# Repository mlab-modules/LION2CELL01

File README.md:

# LION2CELL01D - Li-ion dual-cell Battery Management Module

## Description

The LION2CELL01D is an integrated battery management solution for 18650 Li-ion batteries. It is designed to manage the charging, balancing, and monitoring of two series-connected Li-ion cells. This module measures the remaining energy, voltage, and temperature of the batteries, and protects against over-voltage and over-draining conditions.

## Features

- **Charging and Balancing**: Supports charging, balancing, and termination with temperature protection.
- **Gas-gauging**: Temperature-compensated gas-gauging for accurate remaining energy estimation.
- **Protection**: Over-voltage, over-current protection, but no under-voltage protection (the module operates until battery depletion).
- **Communication**: Supports I2C and HDQ communication interfaces.

## Technical Specifications

- **Power Supply**: 12 V @ 2 A
- **Charging Current**: Factory set to approximately 1.3 A
- **Battery Holder**: 2x 18650
- **Interfaces**: I2C, HDQ
- **Integrated Circuits**:
  - BQ24103 for charging
  - BQ34Z100 for fuel gauging
- **Dimensions**: 80.77 x 60.45 x 16 mm

## Connection

| Pin | Signal | Description       |
|-----|--------|-------------------|
| 1   | PG     | Power Good        |
| 2   | STAT2  | Status Indicator  |
| 3   | GND    | Ground            |
| 4   | CE     | Chip Enable       |
| 5   | STAT1  | Status Indicator  |
| 6   | CMODE  | Configuration Mode|

## Construction

The module is constructed with three main functional blocks:
1. **Charging Circuitry**: Manages the charging process of the two series-connected Li-ion cells.
2. **Measurement Circuitry**: Measures the voltage, current, and temperature of the cells.
3. **Balancing and Protection Circuitry**: Ensures cell voltage balancing and provides protection against over-voltage.

### Important Considerations

- Regular charging is required (at least once every six months) to maintain the batteries within operational voltage ranges.
- Specific resistor values and settings are used for the voltage measurement, ensuring accurate readings without exceeding voltage limits.
- The module is equipped with a balancing circuit that discharges one of the cells to match the voltage of the other, with a discharge current around 10 mA.

## Setup and Configuration

1. **Installation**:
   - Check the PCB for proper soldering.
   - Insert the batteries in the designated order: position 1 first, followed by position 2.
   - Verify the operation of the charging function by connecting a 12V adapter.

2. **Software**:
   - Use `setguage2cell.py` to upload parameters to the energy measurement circuit.
   - Parameters are tailored for Panasonic NCR18650B or INR18650MJ1 cells; adjustments are needed for other types.
   - Conduct at least one charge/discharge cycle for accurate energy measurements.

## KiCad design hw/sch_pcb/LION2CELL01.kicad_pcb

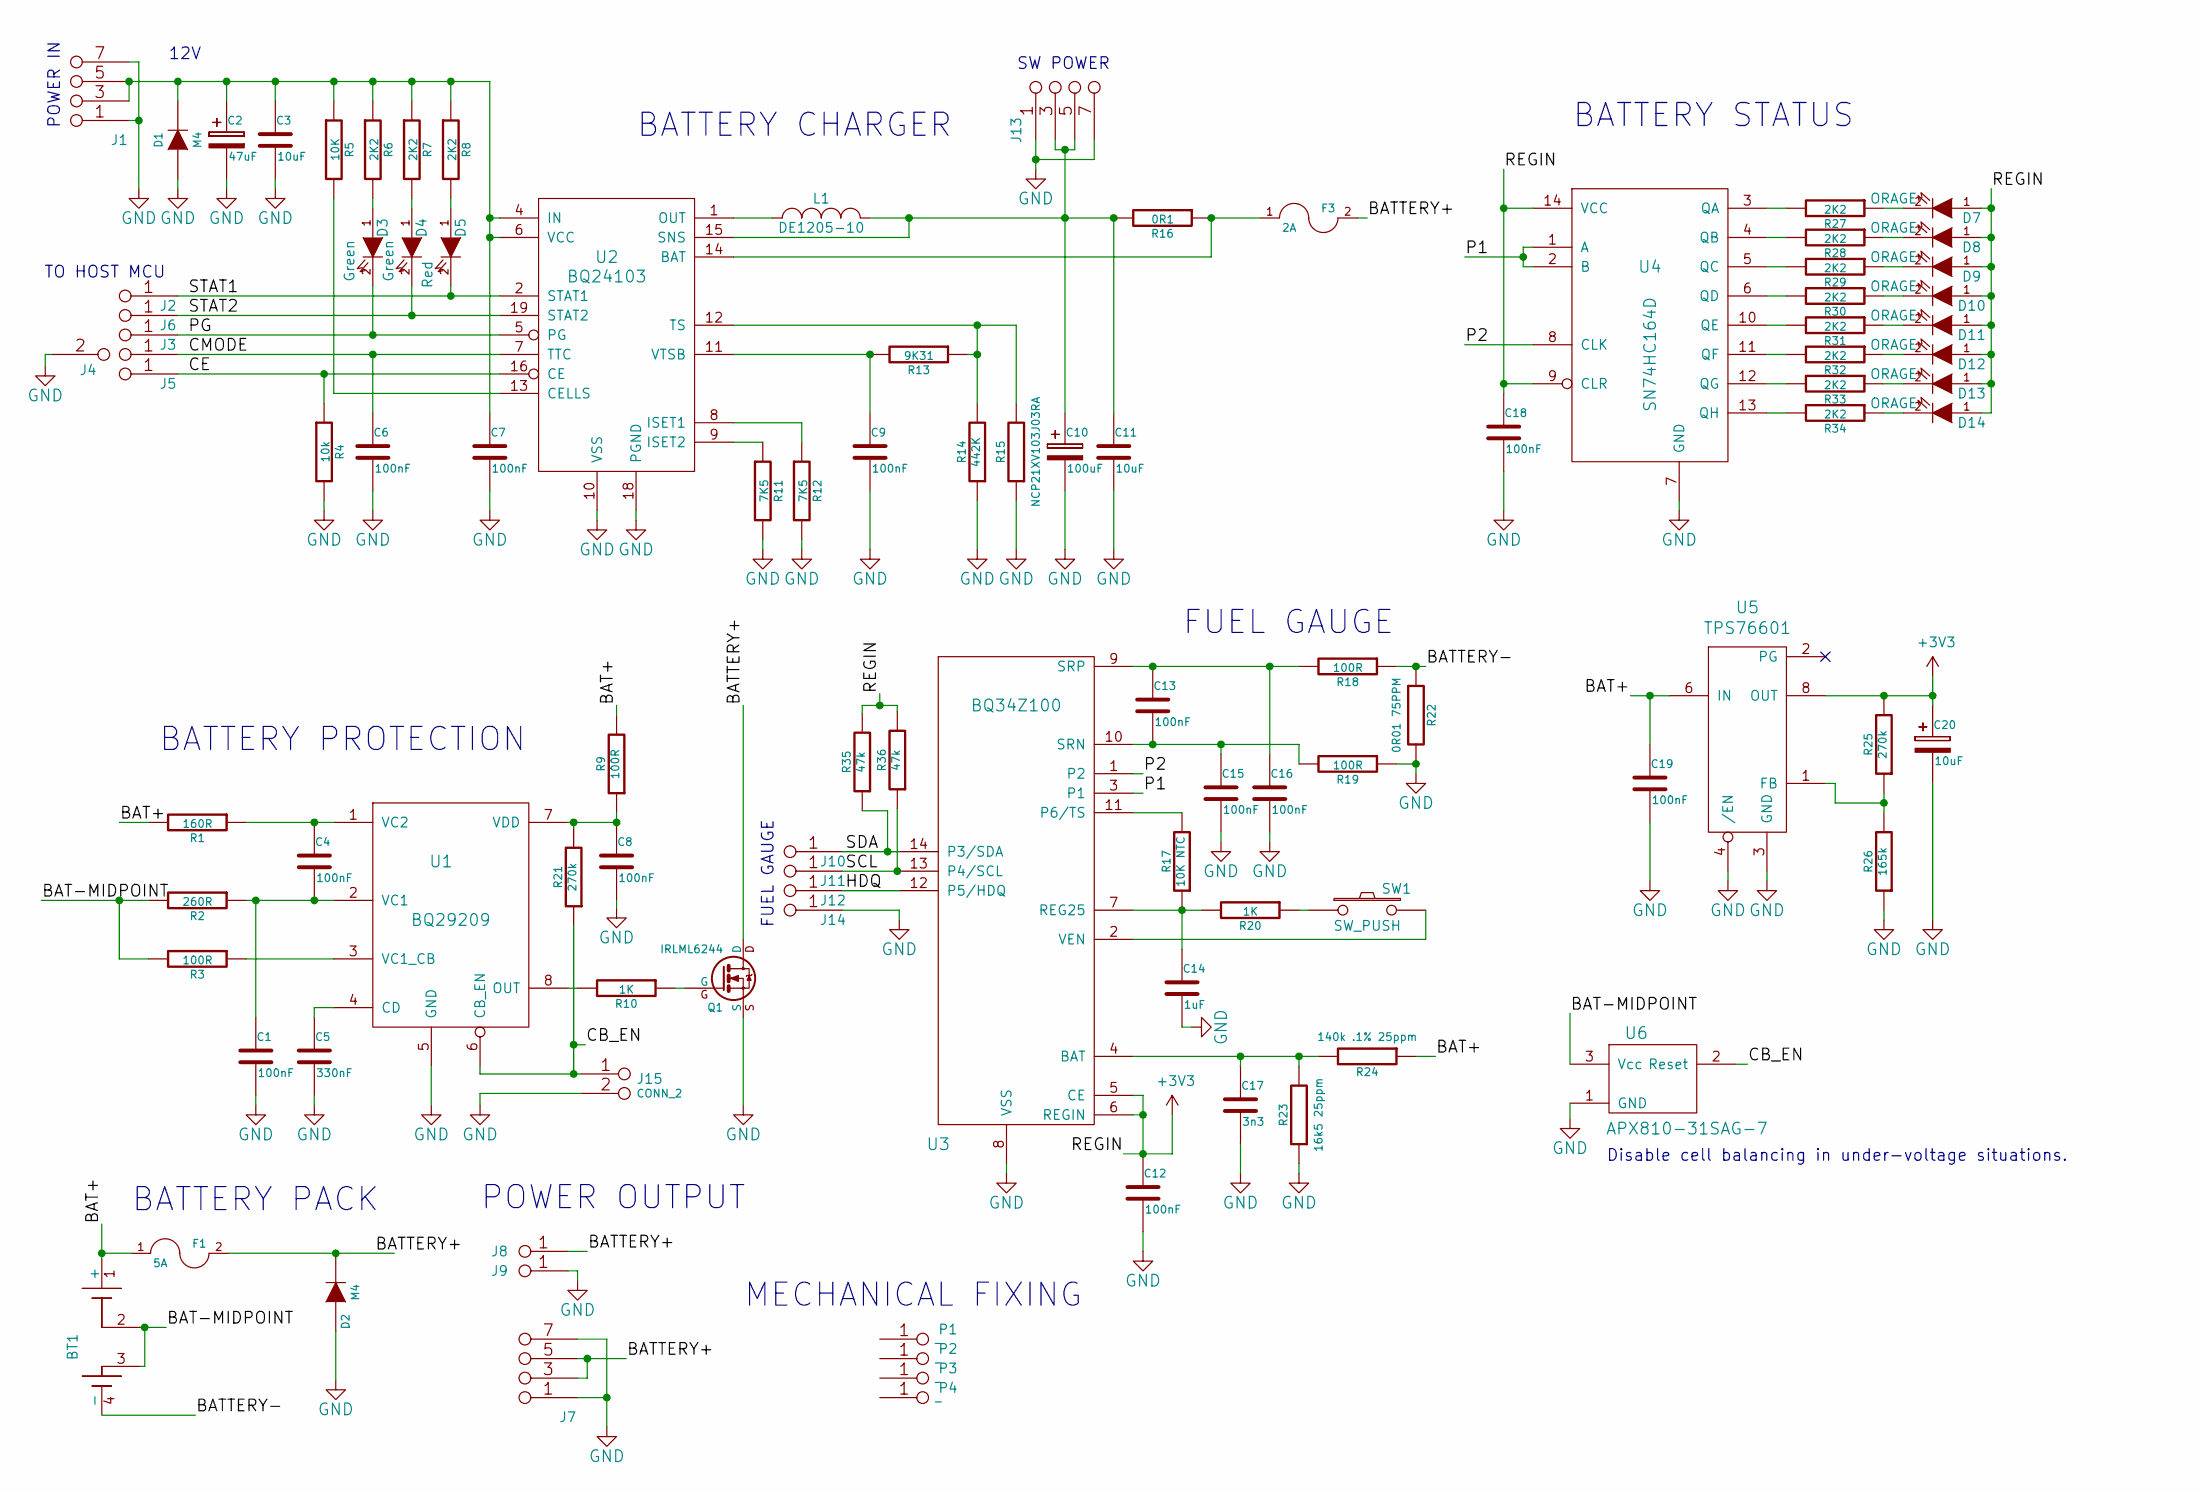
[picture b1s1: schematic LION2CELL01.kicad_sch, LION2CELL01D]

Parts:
BT1: 2x18650_LION-RESCUE-LION2CELL01C; 2LION
C1, C4, C6, C7, C8, C9, C12, C13, C15, C16, C18, C19: 100nF; SMD-0805
C2: 47uF; TantalC_SizeC_Reflow
C3, C11: 10uF; SMD-0805
C5: 330nF; SMD-0805
C10: 100uF; TantalC_SizeD_Reflow
C14: 1uF; SMD-0805
C17: 3n3; SMD-0805
C20: 10uF; TantalC_SizeB_Reflow
D1, D2: M4; SMA_Standard
D3, D4: Green; LED_1206
D5: Red; LED_1206
D7, D8, D9, D10, D11, D12, D13, D14: ORAGE; LED_1206
F1: 5A; Drzak_2410
F3: 2A; Drzak_2410
J1, J7, J13: JUMP_4X2; Straight_2x04
J2, J3, J5, J6, J10, J11, J12, J14: JUMP_2x1; Straight_1x02
J4: JUMP2_2x1
J8, J9: CONN1_1; WAGO256
J15: CONN_2; SMD_1_2x2
L1: DE1205-10
P1, P2, P3, P4: _; MountingHole_3mm
Q1: IRLML6244; SOT-23
R1: 160R; SMD-0805
R2: 260R; SMD-0805
R3, R9, R18, R19: 100R; SMD-0805
R4: 10k; SMD-0805
R5: 10K; SMD-0805
R6, R7, R8, R27, R28, R29, R30, R31, R32, R33, R34: 2K2; SMD-0805
R10, R20: 1K; SMD-0805
R11, R12: 7K5; SMD-0805
R13: 9K31; SMD-0805
R14: 442K; SMD-0805
R15: NCP21XV103J03RA; SMD-0805
R16: 0R1; R_2512
R17: 10K NTC; SMD-0805
R21, R25: 270k; SMD-0805
R22: 0R01 75PPM; SMD-2512
R23: 16k5 25ppm; SMD-0805
R24: 140k .1% 25ppm; SMD-0805
R26: 165k; SMD-0805
R35, R36: 47k; SMD-0805
SW1: SW_PUSH; SW_PUSH_SMALL
U1: BQ29209; VSON-8
U2: BQ24103; VQFN-20
U3: BQ34Z100; TSSOP-14_4.4x5mm_Pitch0.65mm
U4: SN74HC164D; SO-14
U5: TPS76601; SO-8
U6: APX810-31SAG-7; SOT-23

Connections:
+3V3: C12.1, C18.1, C20.1, D7.1 (A), D8.1 (A), D9.1 (A), D10.1 (A), D11.1 (A), D12.1 (A), D13.1 (A), D14.1 (A), R25.2, R35.2, R36.2, U3.5 (CE), U3.6 (REGIN), U4.9 (CLR), U4.14 (VCC), U5.7 (OUT), U5.8 (OUT)
/BAT+: BT1.1 (+), C19.1, F1.1, R1.2, R9.2, R24.1, U5.5 (IN), U5.6 (IN)
/BAT-MIDPOINT: BT1.2, BT1.3, R2.2, R3.2, U6.3 (Vcc)
/BATTERY+: D2.2 (K), F1.2, F3.2, J7.3 (4), J7.4, J7.5, J7.6 (5), J8.1, Q1.D
/BATTERY-: BT1.4 (-), R18.1, R22.1
/CB_EN: J15.1, R21.1, U1.6 (CB_EN), U6.2 (Reset)
/CE: J5.1, J5.2, R4.1, U2.16 (CE)
/CMODE: C6.1, J4.1, U2.7 (TTC)
/HDQ: J12.1, J12.2, U3.12 (P5/HDQ)
/P1: U3.3 (P1), U4.1 (A), U4.2 (B)
/P2: U3.1 (P2), U4.8 (CLK)
/PG: D3.2 (K), J3.1, J3.2, U2.5 (PG)
/SCL: J11.1, J11.2, R36.1, U3.13 (P4/SCL)
/SDA: J10.1, J10.2, R35.1, U3.14 (P3/SDA)
/STAT1: D5.2 (K), J2.1, J2.2, U2.2 (STAT1)
/STAT2: D4.2 (K), J6.1, J6.2, U2.19 (STAT2)
GND: C1.2, C2.2, C3.2, C5.2, C6.2, C7.2, C8.2, C9.2, C10.2, C11.2, C12.2, C14.2, C15.2, C16.2, C17.2, C18.2, C19.2, C20.2, D1.1 (A), D2.1 (A), J1.1 (2), J1.2, J1.7 (8), J1.8, J4.2, J7.1 (2), J7.2, J7.7 (8), J7.8, J9.1, J13.1 (2), J13.2, J13.7 (8), J13.8, J14.1, J14.2, J15.2 (PM), Q1.S, R4.2, R11.2, R12.2, R14.1, R15.1, R19.1, R22.2, R23.1, R26.1, U1.5 (GND), U1.9 (GND), U2.10 (VSS), U2.17 (PGND), U2.18 (PGND), U2.21 (pgnd), U3.8 (VSS), U4.7 (GND), U5.3 (GND), U5.4 (/EN), U6.1 (GND)
unnamed: C1.1, C4.2, R2.1, U1.2 (VC1)
unnamed: C2.1, C3.1, C7.1, D1.2 (K), J1.3 (4), J1.4, J1.5, J1.6 (5), R5.1, R6.1, R7.1, R8.1, U2.3 (IN), U2.4 (IN), U2.6 (VCC)
unnamed: C4.1, R1.1, U1.1 (VC2)
unnamed: C5.1, U1.4 (CD)
unnamed: C8.1, R9.1, R21.2, U1.7 (VDD)
unnamed: C9.1, R13.2, U2.11 (VTSB)
unnamed: C10.1, C11.1, J13.3 (4), J13.4, J13.5, J13.6 (5), L1.2, R16.2, U2.15 (SNS)
unnamed: C13.1, C16.1, R18.2, U3.9 (SRP)
unnamed: C13.2, C15.1, R19.2, U3.10 (SRN)
unnamed: C14.1, R17.1, R20.2, U3.7 (REG25)
unnamed: C17.1, R23.2, R24.2, U3.4 (BAT)
unnamed: D3.1 (A), R6.2
unnamed: D4.1 (A), R7.2
unnamed: D5.1 (A), R8.2
unnamed: D7.2 (K), R27.1
unnamed: D8.2 (K), R28.1
unnamed: D9.2 (K), R29.1
unnamed: D10.2 (K), R30.1
unnamed: D11.2 (K), R31.1
unnamed: D12.2 (K), R32.1
unnamed: D13.2 (K), R33.1
unnamed: D14.2 (K), R34.1
unnamed: F3.1, R16.1, U2.14 (BAT)
unnamed: L1.1, U2.1 (OUT), U2.20 (OUT)
unnamed: Q1.G, R10.1
unnamed: R3.1, U1.3 (VC1_CB)
unnamed: R5.2, U2.13 (CELLS)
unnamed: R10.2, U1.8 (OUT)
unnamed: R11.1, U2.9 (ISET2)
unnamed: R12.1, U2.8 (ISET1)
unnamed: R13.1, R14.2, R15.2, U2.12 (TS)
unnamed: R17.2, U3.11 (P6/TS)
unnamed: R20.1, SW1.1
unnamed: R25.1, R26.2, U5.1 (FB)
unnamed: R27.2, U4.3 (QA)
unnamed: R28.2, U4.4 (QB)
unnamed: R29.2, U4.5 (QC)
unnamed: R30.2, U4.6 (QD)
unnamed: R31.2, U4.10 (QE)
unnamed: R32.2, U4.11 (QF)
unnamed: R33.2, U4.12 (QG)
unnamed: R34.2, U4.13 (QH)
unnamed: SW1.2, U3.2 (VEN)

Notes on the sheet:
BATTERY CHARGER
BATTERY STATUS
BATTERY PACK
POWER OUTPUT
Disable cell balancing in under-voltage situations.
MECHANICAL FIXING
TO HOST MCU
BATTERY PROTECTION
SW POWER
FUEL GAUGE
12V
POWER IN

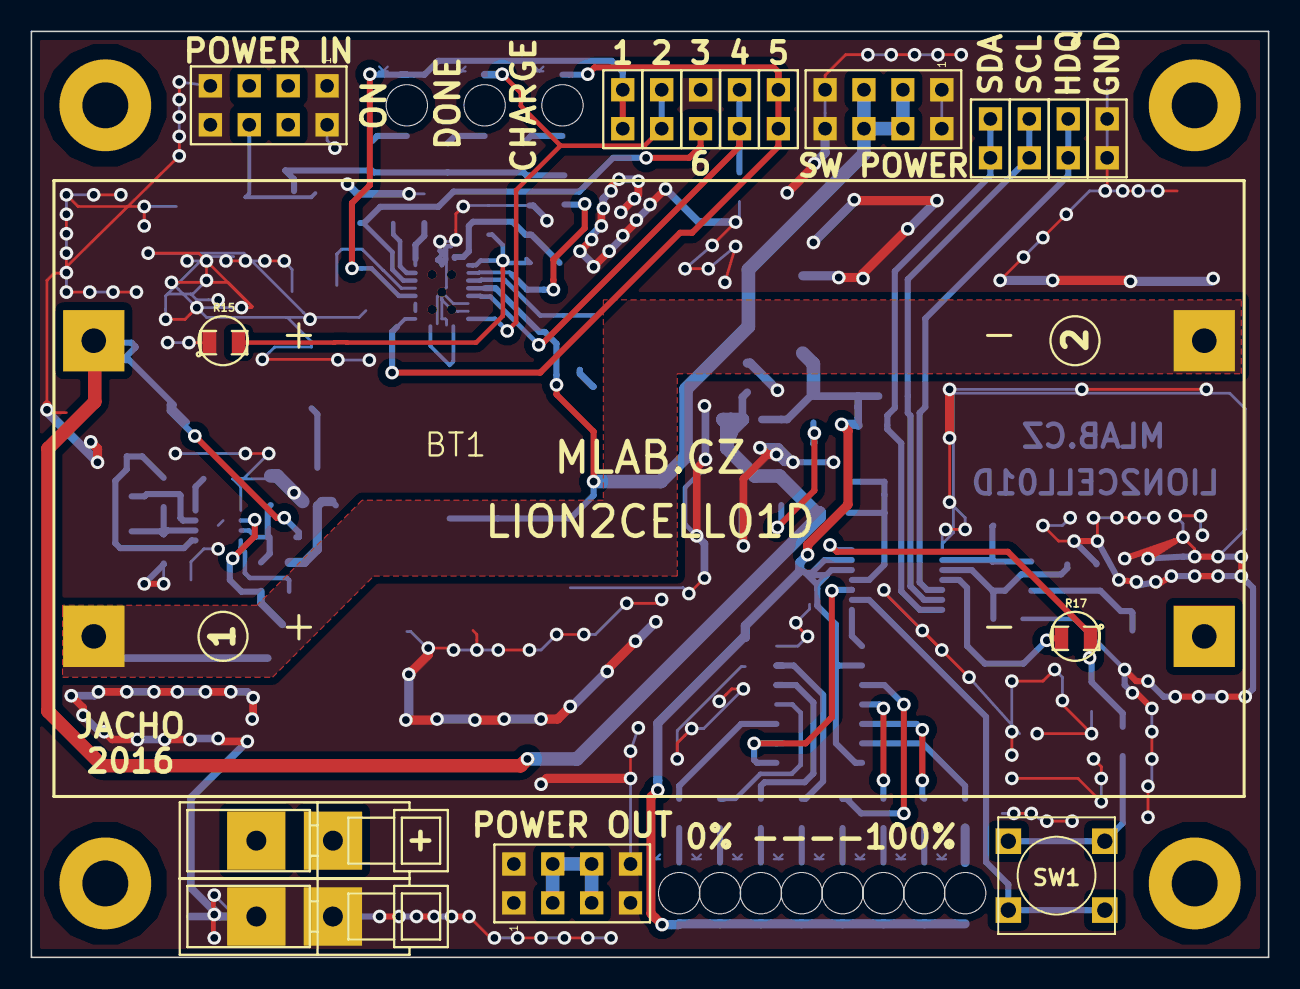
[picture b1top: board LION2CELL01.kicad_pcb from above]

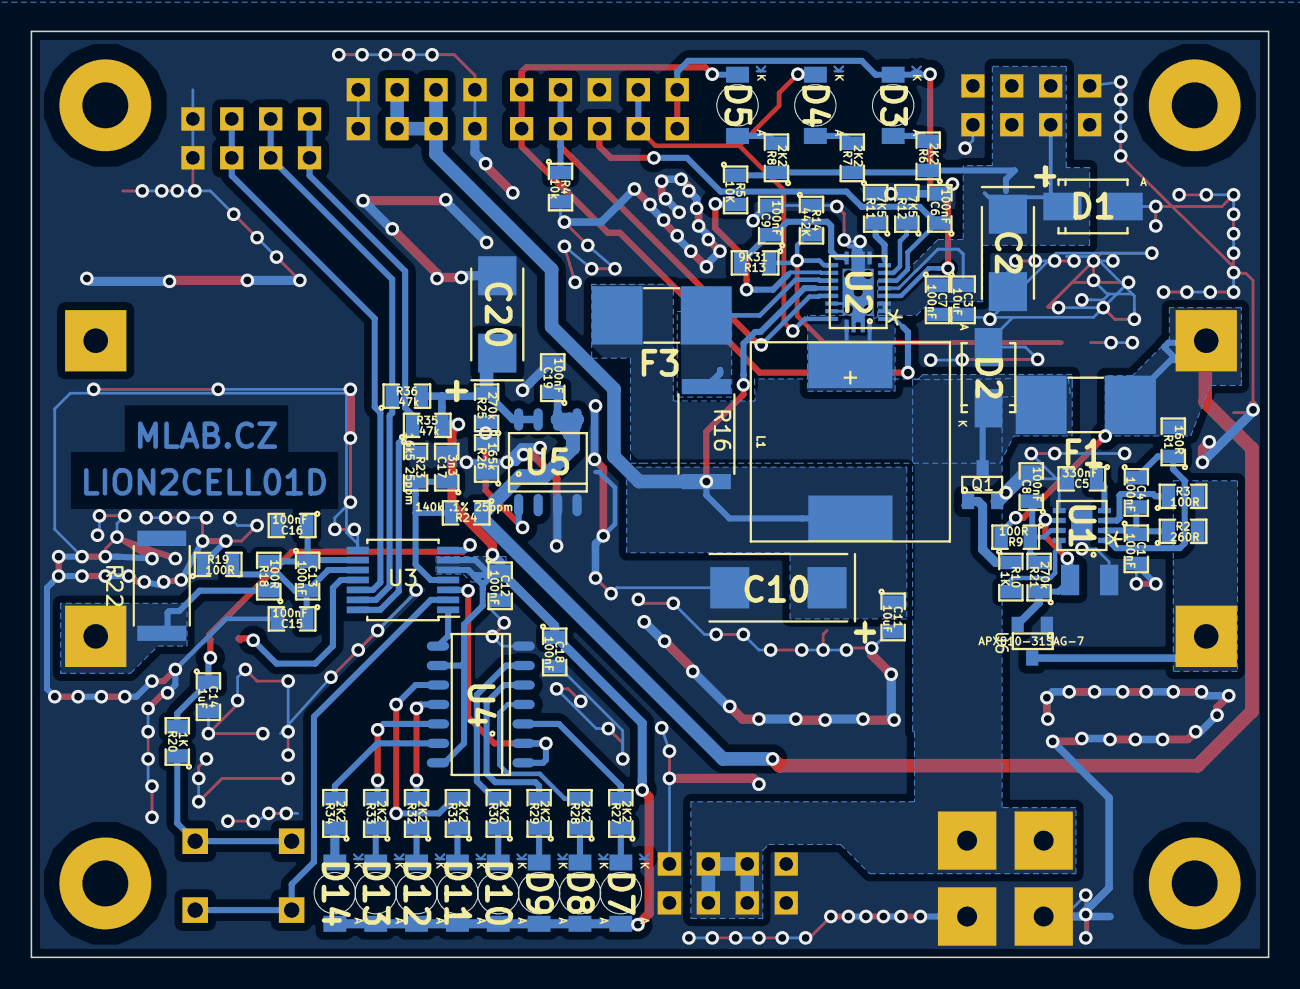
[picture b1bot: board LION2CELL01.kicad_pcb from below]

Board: 2 copper layers, 80.8 x 60.5 mm, 100 parts (78 on the bottom side), 60 nets.

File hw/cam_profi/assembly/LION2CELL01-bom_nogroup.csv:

Component,Description,Part,References,Value,Footprint,Quantity Per PCB,Datasheet
1,,2x18650_LION-RESCUE-LION2CELL01C,BT1,2x18650_LION-RESCUE-LION2CELL01C,2LION,1,
2,,C-RESCUE-LION2CELL01C,C17,3n3,SMD-0805,1,
3,,C-RESCUE-LION2CELL01C,C1C4C6C7C8C9C12C13C15C16C18C19,100nF,SMD-0805,12,
4,,C-RESCUE-LION2CELL01C,C5,330nF,SMD-0805,1,
5,,C-RESCUE-LION2CELL01C,C14,1uF,SMD-0805,1,
6,,C-RESCUE-LION2CELL01C,C3C11,10uF,SMD-0805,2,
7,,CP2,C20,10uF,TantalC_SizeB_Reflow,1,
8,,CP2,C2,47uF,TantalC_SizeC_Reflow,1,
9,,CP2,C10,100uF,TantalC_SizeD_Reflow,1,
10,,LED-RESCUE-LION2CELL01C,D3D4,Green,LED_1206,2,
11,,DIODE,D1D2,M4,SMA_Standard,2,
12,,LED-RESCUE-LION2CELL01C,D7D8D9D10D11D12D13D14,ORAGE,LED_1206,8,
13,,LED-RESCUE-LION2CELL01C,D5,Red,LED_1206,1,
14,,FUSE,F3,2A,Drzak_2410,1,
15,,FUSE,F1,5A,Drzak_2410,1,
16,,CONN1_1,J8J9,CONN1_1,WAGO256,2,
17,,CONN_2,J15,CONN_2,SMD_1_2x2,1,
18,,JUMP2_2x1,J4,JUMP2_2x1,,1,
19,,JUMP_2x1,J2J3J5J6J10J11J12J14,JUMP_2x1,Straight_1x02,8,
20,,JUMP_4X2,J1J7J13,JUMP_4X2,Straight_2x04,3,
21,,INDUCTOR_SMALL,L1,DE1205-10,DE1205-10,1,
22,,MOSFET-N,Q1,IRLML6244,SOT-23,1,
23,,R-RESCUE-LION2CELL01C,R16,0R1,R_2512,1,
24,,R-RESCUE-LION2CELL01C,R3R9R18R19,100R,SMD-0805,4,
25,,R-RESCUE-LION2CELL01C,R1,160R,SMD-0805,1,
26,,R-RESCUE-LION2CELL01C,R2,260R,SMD-0805,1,
27,,R-RESCUE-LION2CELL01C,R10R20,1K,SMD-0805,2,
28,,R-RESCUE-LION2CELL01C,R6R7R8R27R28R29R30R31R32R33R34,2K2,SMD-0805,11,
29,,R-RESCUE-LION2CELL01C,R11R12,7K5,SMD-0805,2,
30,,R-RESCUE-LION2CELL01C,R13,9K31,SMD-0805,1,
31,,R-RESCUE-LION2CELL01C,R4R5,10k,SMD-0805,2,
32,,R-RESCUE-LION2CELL01C,R35R36,47k,SMD-0805,2,
33,,R-RESCUE-LION2CELL01C,R26,165k,SMD-0805,1,
34,,R-RESCUE-LION2CELL01C,R21R25,270k,SMD-0805,2,
35,,R-RESCUE-LION2CELL01C,R14,442K,SMD-0805,1,
36,,R-RESCUE-LION2CELL01C,R22,0R01 75PPM,SMD-2512,1,
37,,R-RESCUE-LION2CELL01C,R17,10K NTC,SMD-0805,1,
38,,R-RESCUE-LION2CELL01C,R24,140k .1% 25ppm,SMD-0805,1,
39,,R-RESCUE-LION2CELL01C,R23,16k5 25ppm,SMD-0805,1,
40,,R-RESCUE-LION2CELL01C,R15,NCP21XV103J03RA,SMD-0805,1,
41,,SW_PUSH,SW1,SW_PUSH,SW_PUSH_SMALL,1,
42,,APX810-31SAG-7,U6,APX810-31SAG-7,SOT-23,1,
43,,BQ24103,U2,BQ24103,VQFN-20,1,
44,,BQ29209,U1,BQ29209,VSON-8,1,https://www.ti.com/lit/ds/symlink/bq29209.pdf
45,,BQ34Z100,U3,BQ34Z100,TSSOP-14_4.4x5mm_Pitch0.65mm,1,
46,,SN74HC164D,U4,SN74HC164D,SO-14,1,
47,,TPS76601,U5,TPS76601,SO-8,1,

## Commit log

2017-08-22 rename category folders
2017-08-22 rename files and module folders
2017-08-22 change images path
2017-08-22 create hw folder
2017-08-22 change filepaths
2017-08-22 rm empty json html files, rename module.json files
2017-08-22 new .json files
2017-11-02 [MLABweb] 2017-11-02 23:14:20 LION2CELL01D
2017-11-02 [MLABweb] 2017-11-02 23:37:45 LION2CELL01D
2017-11-02 [MLABweb] 2017-11-02 23:38:01 LION2CELL01D
2017-11-16 [MLABweb] 2017-11-16 10:46:03 LION2CELL01B
2017-11-16 [MLABweb] 2017-11-16 10:46:18 LION2CELL01C
2017-12-08 A thermal images of LION2CELL modules.
2017-12-28 Code style cleanup.
2018-04-12 [MLABweb] Documentaion edits; LION2CELL01B
2018-11-05 Presun obrazku do slozky img. Pregenerovani dokumentaci.
2020-05-04 The basic photos of new modules.
2020-10-30 Documentation update.
2021-05-11 Documentation cleanup.
2021-05-11 Update scripts to python3 compatibility. Documentation update.
2021-05-12 Generování PDF popisků
2021-05-17 Manufacturing documentation improvement.
2021-05-31 Switch driver selection to hid.
2021-05-31 Adding a new gcode sliced for prusa Mini+
2021-05-31 Add gcode for Be3D edee printer.
2021-06-02 Update documentation. Improve schematic (title block, texts) Regenerate PDF export.
2021-06-12 Add information about charging current.
2022-02-17 MLAB web edit.
2022-04-06 automated commit; add github actions
2022-04-06 Update actions products
2022-07-20 Update title block and assets submodule.
2023-05-25 Update metadata files
2023-05-28 Update workflow files
2023-07-05 automated commit; rename source files to new naming convence
2023-09-16 Update image to image_title
2023-09-16 Update status
2024-07-17 Update to KiCADv8 project.
